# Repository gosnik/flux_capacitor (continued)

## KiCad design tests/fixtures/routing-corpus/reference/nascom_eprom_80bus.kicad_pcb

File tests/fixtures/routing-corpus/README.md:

# Real-board routing corpus

This directory replaces Flux's generated 4--20 component routing boards with a deliberately small
progression derived from the open-source
[KiCadRoutingTools stress corpus](https://github.com/drandyhaas/KiCadRoutingTools/tree/main/tests/stress)
and its [real-board routing discussion](https://github.com/drandyhaas/KiCadRoutingTools/discussions/117).

The important policy is monotonic progressive activation. A qualified tier always remains in the
routine run, and permanently unlocks the next tier as the single capability probe. Higher
levels remain available for focused inspection, but are not silently added to every build merely
because their files exist.

| Level | Board | Upstream stress set | Current gate | Purpose |
| ---: | --- | --- | --- | --- |
| 0 | `pt2399_delay` | set13 | mandatory, passing | Requalified under original project rules; 50 connections, zero errors/opens; straight tracks |
| 1 | `bm_svf` | set15 | unlocked | Always-run analog module probe; 78 seeded connections with residual overflow |
| 2 | `ft2232h_jtag` | set5 | locked | 117 connections; compact 64-pin USB/JTAG fanout |
| 3 | `gb_nintendo_power` | set24 | locked | 148 connections; 80-pad IC and parallel memory buses |
| 4 | `nascom_eprom_80bus` | set23 | locked | 415 connections; repeated DIP sockets and card-edge bus |

`manifest.json` is authoritative for source repository, exact commit, original path, license,
source hash, prepared-board hash, routed-reference hash, project hash, inventory, and current gate.
The board beside each project is the stripped routing input. `reference/` contains the normalized
human-routed board so later quality grading can compare against ground truth rather than assuming
zero source DRC findings. Full upstream license texts are under `licenses/`.

The 2026-09-06 rule-context audit found that the final DRC candidate lacked its
sibling project and was checked under KiCad defaults. The unchanged Tier-0 copper
has 199 track-width and 9 drill-spacing errors under the original project, with
zero opens. The manifest keeps Tier 0's mandatory `qualified` gate so the corrected
test fails visibly; it has not been downgraded to hide the regression. Tier 0 must
be genuinely recovered before promoting Tier 1. See
`reports/diagnoses/2026-09-06-tier0-project-rule-context.json` at the repository root.

Tier 0 was genuinely restored on 2026-09-07 after source-rule import, source-hole
preservation, committed-context retries and run-aligned PH corner seeds. The
curved-mode corpus invocation at that point passed: 82 tracks, 152 arcs, four vias, zero
unfinished bends and clean original-project KiCad DRC. An unspecified CLI pitch
is raised to the shared validator's source-rule floor; explicit values remain
validated. See `reports/benchmark_history/2026-09-07-default-rule-pitch.json`.
Tier 1 remains the frontier; its latest 600-second diagnostic probe timed out in
regional repair, and its 78 selected paths are not legal final copper.

## Preparation

The inputs were prepared from pinned upstream revisions with KiCadRoutingTools commit
`661c88b3c3b0ebc9ade65eab63d30b1cde217fb4`, using `tests/stress/prep_set2.py` and pcbnew 9.0.8.
The only compatibility adjustment supplied a null error-handler argument to the KiCad 9
`GetBoardPolygonOutlines` overload. Preparation normalized the source, removed tracks, vias and
copper zones, retained rule areas, rebuilt Edge.Cuts, removed non-routing graphics, and preserved
the sibling project settings. This is recorded in the manifest rather than treated as upstream
source identity.

## Running the progression

The ordinary test runs every qualified tier plus the first unlocked tier:

```sh
ctest --test-dir build/dev -R flux_cli_routing_corpus_unlocked --output-on-failure
```

Inspect progressively larger capability levels without routing every board:

```sh
python3 tests/python/verify_routing_corpus.py \
  --flux-cli build/dev/flux-cli \
  --corpus tests/fixtures/routing-corpus \
  --level 2
```

`--level all` verifies provenance and strict import for the whole curated set. Locked tiers are not
routed unless they become unlocked. A qualified board must keep completing; the unlocked board
always receives a bounded routing attempt. If that attempt satisfies its qualification target, the
harness fails with an explicit promotion request: change it from `unlocked` to `qualified` and
change the next locked tier to `unlocked` in the same revision. This makes unlocking permanent
without allowing a test process to mutate policy. The source and reference files are hashed before
and after every run.

Every tier now requires `detailed_complete`; a zero-overflow global plan alone cannot trigger
promotion. `detailed_complete` is the final-copper qualification. Such a tier must produce an
exported KiCad
board with zero structural errors, open connections, and represented copper violations. Only after
those exact gates and an error-level external KiCad DRC pass does the harness render one
2400-pixel PNG per enabled copper layer (with `Edge.Cuts` as context) under the configured artifact
directory. Incomplete previews are never labelled or rendered as final copper. CTest writes these review artifacts below
`build/release/tests/routing-corpus-artifacts/`.

Final DRC now requires a byte-identical project and any custom-rule sidecar under
the candidate's basename. Their hashes are recorded in `kicad-drc.context.json`.
They are also published beside accepted copper. Rejected copper and its rule
context are retained under `analysis/kicad-drc-rejected`, not as final output.

Every tier run records diagnostic telemetry and writes bounded, non-authoritative analysis PNGs
under `artifacts/tier-<level>-<board>/analysis`. The images are emitted for successful,
incomplete, and timed-out routing attempts. `--failed-route-png-dir` remains available only to
override that analysis root, for example:

```sh
python3 tests/python/verify_routing_corpus.py \
  --flux-cli build/dev/flux-cli \
  --corpus tests/fixtures/routing-corpus \
  --board bm_svf \
  --failed-route-png-dir build/failed-route-previews \
  --failed-route-png-mode both \
  --max-failed-route-png-results 8
```

The harness ranks completed regional candidates by topology
and mutual-clearance failures, and writes layer copper, whole provisional-board, full-context
quintic PH Bezier controls, and automatically cropped control close-ups. A JSON manifest records the candidate/window identity and explicitly marks
the output as diagnostic rather than accepted copper. `copper` and `spline` modes may be selected
individually. Rendering also runs after a board timeout, using every complete telemetry event that
was flushed before cancellation.

Useful KiCadRoutingTools ideas retained in Flux's harness are immutable pinned sources, paired
human references, manifest provenance, bounded per-board execution, deterministic replay inputs,
and progressive corpus qualification. Their large queue/agent orchestration is intentionally not
copied into the routine test path.

The current default is straight-section routing. Tier 0 has been rechecked repeatedly:
243 horizontal/vertical/45-degree tracks, zero arcs, five vias, all 50 connections and clean
original-project KiCad DRC. The runner independently audits exported segment angles. The arc-count and rounded-bend requirements are retained in `curved_expected`
and selected by `./run_tiers.sh --track-geometry curved`. Fabrication, connectivity and
external DRC requirements are identical in both modes. Tier 1 remains unqualified.
See `reports/benchmark_history/2026-09-07-tier-resolution/summary.json` for the current
experiments and `reports/benchmark_history/2026-09-07-straight-routing-summary.json` for
the earlier straight-mode baseline and rejected controls.

## Adopted alternative boards

A separately staged [alternative Tier 2–4 corpus](alternatives/README.md) contains
FT2232H JTAG/UART, Nintendo Power cartridge and Nascom EPROM inputs with clean
strict-import and stripped-board DRC checks. Selection evidence and reference
caveats are documented there. These boards now replace the source-blocked levels 2–4 in the active manifest;
all remain locked and unqualified. The former Zigbee, CH32V003 and USB-GPIB
inputs remain in `compatibility/manifest.json` as source-compatibility regressions.
The existing Tier-0 and Tier-1 entries are byte-for-byte equivalent JSON objects.
New boards carry their KRT preparation revision per entry; initial provenance
above continues to describe levels 0–1 and the compatibility corpus.

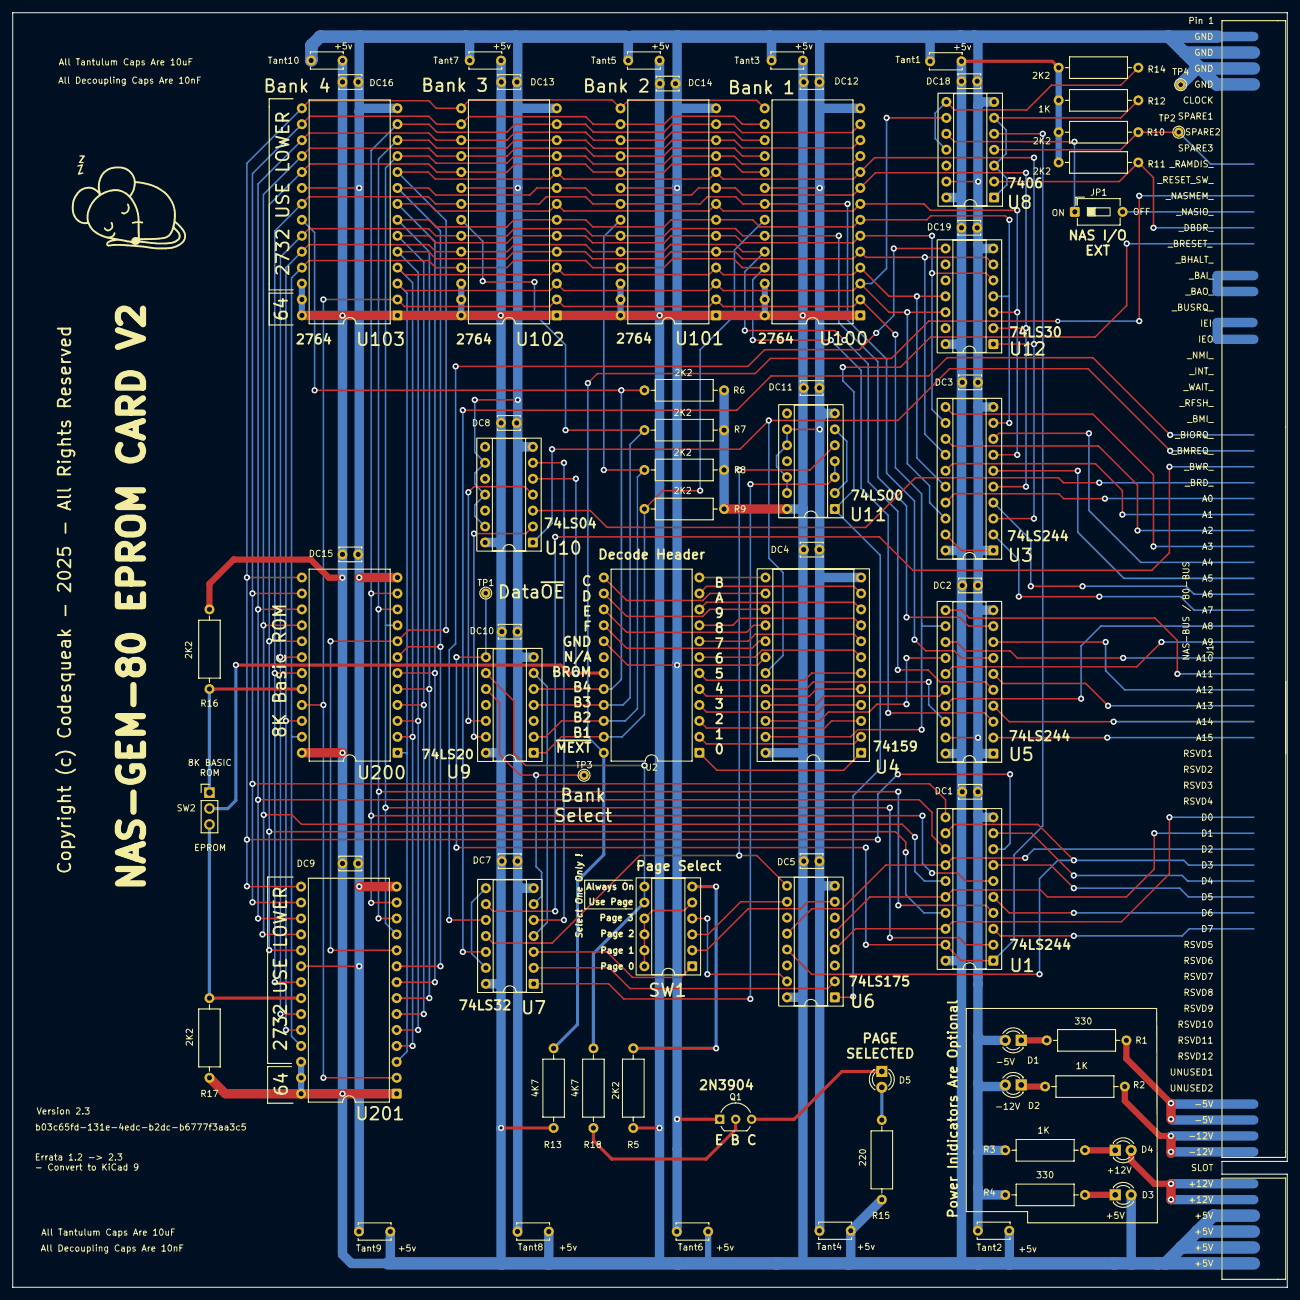
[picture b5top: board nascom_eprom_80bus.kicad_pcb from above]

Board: 2 copper layers, 203.2 x 203.2 mm, 79 parts (1 on the bottom side), 116 nets.

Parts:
D1, D2, D3, D4, D5: LED; LED_D3.0mm
DC1, DC2, DC3, DC4, DC5, DC7, DC8, DC9, DC10, DC11, DC12, DC13, DC14, DC15, DC16, DC18, DC19: 10nF; C_Disc_D3.4mm_W2.1mm_P2.50mm
G1: LOGO; sleepymouse_small
G001: LOGO; qr-code
J1: Conn_01x80NasBus; 80BusEdgeConnector
JP1: Link 1; SW_DIP_SPSTx01_Slide_6.7x4.1mm_W7.62mm_P2.54mm_LowProfile
Q1: 2N3904; TO-92_Inline_Wide
R1, R4, R15: 330; R_Axial_DIN0309_L9.0mm_D3.2mm_P12.70mm_Horizontal
R2, R3: 1k; R_Axial_DIN0309_L9.0mm_D3.2mm_P12.70mm_Horizontal
R5, R6, R7, R8, R9, R10, R11, R14, R16, R17: 2K2; R_Axial_DIN0309_L9.0mm_D3.2mm_P12.70mm_Horizontal
R12: 1K; R_Axial_DIN0309_L9.0mm_D3.2mm_P12.70mm_Horizontal
R13, R18: 4K7; R_Axial_DIN0309_L9.0mm_D3.2mm_P12.70mm_Horizontal
SW1: SW_DIP_x06; DIP-12_W7.62mm_Socket
SW2: SW_SPDT; PinHeader_1x03_P2.54mm_Vertical
TP1: Data ~OE~; TestPoint_THTPad_D1.5mm_Drill0.7mm
TP2: ~RAMDIS~; TestPoint_THTPad_D1.5mm_Drill0.7mm
TP3: Bank Select; TestPoint_THTPad_D1.5mm_Drill0.7mm
TP4: 0V / Ground; TestPoint_THTPad_D1.5mm_Drill0.7mm
Tant1, Tant2, Tant3, Tant4, Tant5, Tant6, Tant7, Tant8, Tant9, Tant10: 10uF; C_Disc_D5.0mm_W2.5mm_P5.00mm
U1, U3, U5: 74LS244; DIP-20_W7.62mm_Socket
U2: DecodeHeader; DIP-24_W15.24mm
U4: 74159; DIP-24_W15.24mm_Socket
U6: 74LS175; DIP-16_W7.62mm_Socket
U7: 74LS32; DIP-14_W7.62mm_Socket
U8: 7406; DIP-14_W7.62mm_Socket
U9: 74LS20; DIP-14_W7.62mm_Socket
U10: 74LS04; DIP-14_W7.62mm_Socket
U11: 74LS00; DIP-14_W7.62mm_Socket
U12: 74LS30; DIP-14_W7.62mm_Socket
U100, U101, U102, U103, U201: 2764; DIP-28_W15.24mm
U200: MK36000_8K_ROM; DIP-24_W15.24mm

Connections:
8K_ROM: SW2.2 (B), U2.19 (~8KROM), U10.5
+12V: D4.2 (A), J1.73 (Pin_73_+12v), J1.74 (Pin_74_+12v)
-5V: J1.68 (Pin_68_-5v), J1.69 (Pin_69_-5v), R1.2
-12V: J1.70 (Pin_70_-12v), J1.71 (Pin_71_-12v), R2.2
/BA0: U3.3 (O3b), U12.1, U100.10 (A0), U101.10 (A0), U102.10 (A0), U103.10 (A0), U200.8 (A0), U201.10 (A0)
/BA1: U3.5 (O2b), U12.2, U100.9 (A1), U101.9 (A1), U102.9 (A1), U103.9 (A1), U200.7 (A1), U201.9 (A1)
/BA2: U3.7 (O1b), U12.3, U100.8 (A2), U101.8 (A2), U102.8 (A2), U103.8 (A2), U200.6 (A2), U201.8 (A2)
/BA3: U3.9 (O0b), U12.4, U100.7 (A3), U101.7 (A3), U102.7 (A3), U103.7 (A3), U200.5 (A3), U201.7 (A3)
/BA4: U3.12 (O3a), U12.5, U100.6 (A4), U101.6 (A4), U102.6 (A4), U103.6 (A4), U200.4 (A4), U201.6 (A4)
/BA5: U3.14 (O2a), U12.6, U100.5 (A5), U101.5 (A5), U102.5 (A5), U103.5 (A5), U200.3 (A5), U201.5 (A5)
/BA6: U3.16 (O1a), U12.11, U100.4 (A6), U101.4 (A6), U102.4 (A6), U103.4 (A6), U200.2 (A6), U201.4 (A6)
/BA7: U3.18 (O0a), U8.9, U12.12, U100.3 (A7), U101.3 (A7), U102.3 (A7), U103.3 (A7), U200.1 (A7), U201.3 (A7)
/BA8: U5.3 (O3b), U100.25 (A8), U101.25 (A8), U102.25 (A8), U103.25 (A8), U200.23 (A8), U201.25 (A8)
/BA9: U5.5 (O2b), U100.24 (A9), U101.24 (A9), U102.24 (A9), U103.24 (A9), U200.22 (A9), U201.24 (A9)
/BA10: U5.7 (O1b), U100.21 (A10), U101.21 (A10), U102.21 (A10), U103.21 (A10), U200.19 (A10), U201.21 (A10)
/BA11: U5.9 (O0b), U100.23 (A11), U101.23 (A11), U102.23 (A11), U103.23 (A11), U200.18 (A11), U201.23 (A11)
/BA12: U4.23 (A0), U5.12 (O3a), U100.2 (A12), U101.2 (A12), U102.2 (A12), U103.2 (A12), U200.21 (A12), U201.2 (A12)
/BD0: U1.2 (I0a), U100.11 (D0), U101.11 (D0), U102.11 (D0), U103.11 (D0), U200.9 (DQ0), U201.11 (D0)
/BD1: U1.4 (I1a), U100.12 (D1), U101.12 (D1), U102.12 (D1), U103.12 (D1), U200.10 (DQ1), U201.12 (D1)
/BD2: U1.6 (I2a), U100.13 (D2), U101.13 (D2), U102.13 (D2), U103.13 (D2), U200.11 (DQ2), U201.13 (D2)
/BD3: U1.8 (I3a), U100.15 (D3), U101.15 (D3), U102.15 (D3), U103.15 (D3), U200.13 (DQ3), U201.15 (D3)
/BD4: U1.11 (I0b), U100.16 (D4), U101.16 (D4), U102.16 (D4), U103.16 (D4), U200.14 (DQ4), U201.16 (D4)
/BD5: U1.13 (I1b), U100.17 (D5), U101.17 (D5), U102.17 (D5), U103.17 (D5), U200.15 (DQ5), U201.17 (D5)
/BD6: U1.15 (I2b), U100.18 (D6), U101.18 (D6), U102.18 (D6), U103.18 (D6), U200.16 (DQ6), U201.18 (D6)
/BD7: U1.17 (I3b), U100.19 (D7), U101.19 (D7), U102.19 (D7), U103.19 (D7), U200.17 (DQ7), U201.19 (D7)
A0: J1.30, U3.17 (I3b)
A1: J1.31, U3.15 (I2b)
A2: J1.32, U3.13 (I1b)
A3: J1.33, U3.11 (I0b)
A4: J1.34, U3.8 (I3a)
A5: J1.35, U3.6 (I2a)
A6: J1.36, U3.4 (I1a)
A7: J1.37, U3.2 (I0a)
A8: J1.38, U5.17 (I3b)
A9: J1.39, U5.15 (I2b)
A10: J1.40, U5.13 (I1b)
A11: J1.41, U5.11 (I0b)
A12: J1.42, U5.8 (I3a)
A13: J1.43, U5.6 (I2a)
A14: J1.44, U5.4 (I1a)
A15: J1.45, U5.2 (I0a)
Bank1: R9.1, U2.23 (~Bank1), U9.1, U100.22 (~OE)
Bank2: R8.1, U2.22 (~Bank2), U9.2, U101.22 (~OE)
Bank3: R7.1, U2.21 (~Bank3), U9.4, U102.22 (~OE)
Bank4: R6.1, U2.20 (~Bank4), U9.5, U103.22 (~OE)
D0: J1.50, U1.18 (O0a), U6.4 (D0)
D1: J1.51, U1.16 (O1a), U6.5 (D1)
D2: J1.52, U1.14 (O2a), U6.12 (D2)
D3: J1.53, U1.12 (O3a), U6.13 (D3)
D4: J1.54, U1.9 (O0b)
D5: J1.55, U1.7 (O1b)
D6: J1.56, U1.5 (O2b)
D7: J1.57, U1.3 (O3b)
GND: D1.2 (A), D2.2 (A), DC1.2, DC2.2, DC3.2, DC4.2, DC5.2, DC7.2, DC8.2, DC9.2, DC10.2, DC11.2, DC12.2, DC13.2, DC14.2, DC15.2, DC16.2, DC18.2, DC19.2, J1.1 (Pin_1_0v), J1.2 (Pin_2_0v), J1.3 (Pin_3_0v), J1.4 (Pin_4_0v), Q1.1 (E), R3.2, R4.2, TP4.1, Tant1.2, Tant2.2, Tant3.2, Tant4.2, Tant5.2, Tant6.2, Tant7.2, Tant8.2, Tant9.2, Tant10.2, U1.10 (GND), U2.17 (GND), U3.1 (OEa), U3.10 (GND), U3.19 (OEb), U4.12 (GND), U4.18 (~E0), U5.1 (OEa), U5.10 (GND), U5.19 (OEb), U6.8 (GND), U7.7 (GND), U8.7 (GND), U8.13, U9.7 (GND), U10.7 (GND), U10.9, U10.11, U10.13, U11.7 (GND), U11.9, U11.10, U11.12, U11.13, U12.7 (GND), U100.14 (GND), U100.20 (~CE), U101.14 (GND), U101.20 (~CE), U102.14 (GND), U102.20 (~CE), U103.14 (GND), U103.20 (~CE), U200.12 (VSS), U201.14 (GND), U201.20 (~CE)
unnamed: D1.1 (K), R1.1
unnamed: D2.1 (K), R2.1
unnamed: D3.1 (K), R4.1
unnamed: D4.1 (K), R3.1
unnamed: D5.2 (A), R15.2
unnamed: D5.1 (K), Q1.3 (C)
unnamed: J1.16, J1.17
unnamed: J1.19, J1.20
unnamed: JP1.1 (A), U8.10
unnamed: Q1.2 (B), R18.1
unnamed: R5.2, SW1.6
unnamed: R12.2, U8.1, U8.3, U8.6
unnamed: R14.1, U8.8, U8.11
unnamed: R18.2, SW1.7, SW1.8, U9.9
unnamed: SW1.1, U7.3
unnamed: SW1.5, SW1.9, SW1.10, SW1.11, SW1.12
unnamed: R16.2, SW2.1 (A), U200.20 (~OE)
unnamed: R17.2, SW2.3 (C), U201.22 (~OE)
unnamed: TP3.1, U7.6, U9.10
unnamed: TP1.1, U1.1 (OEa), U1.19 (OEb), U8.5, U9.8
unnamed: U2.1 (Block0), U4.1 (~S0)
unnamed: U2.2 (Block1), U4.2 (~S1)
unnamed: U2.3 (Block2), U4.3 (~S2)
unnamed: U2.4 (Block3), U4.4 (~S3)
unnamed: U2.5 (Block4), U4.5 (~S4)
unnamed: U2.6 (Block5), U4.6 (~S5)
unnamed: U2.7 (Block6), U4.7 (~S6)
unnamed: U2.8 (Block7), U4.8 (~S7)
unnamed: U2.9 (Block8), U4.9 (~S8)
unnamed: U2.10 (Block9), U4.10 (~S9)
unnamed: U2.11 (BlockA), U4.11 (~S10)
unnamed: U2.12 (BlockB), U4.13 (~S11)
unnamed: U2.13 (BlockC), U4.14 (~S12)
unnamed: U2.14 (BlockD), U4.15 (~S13)
unnamed: U2.15 (BlockE), U4.16 (~S14)
unnamed: U2.16 (BlockF), U4.17 (~S15)
unnamed: U4.22 (A1), U5.14 (O2a)
unnamed: U4.21 (A2), U5.16 (O1a)
unnamed: U4.20 (A3), U5.18 (O0a)
unnamed: U6.9 (Cp), U7.11, U11.5
unnamed: U6.2 (Q0), U7.2
unnamed: SW1.2, U6.7 (Q1)
unnamed: SW1.3, U6.10 (Q2)
unnamed: SW1.4, U6.15 (Q3)
unnamed: U7.4, U9.6
unnamed: U7.8, U7.13
unnamed: U9.13, U10.2
unnamed: U9.12, U10.4
unnamed: U7.5, U10.6
unnamed: U11.2, U11.6
unnamed: U7.10, U12.8
PAGE_0: U7.1, U11.3, U11.4
VCC: D3.2 (A), DC1.1, DC2.1, DC3.1, DC4.1, DC5.1, DC7.1, DC8.1, DC9.1, DC10.1, DC11.1, DC12.1, DC13.1, DC14.1, DC15.1, DC16.1, DC18.1, DC19.1, J1.75 (Pin_75_+5v), J1.76 (Pin_76_+5v), J1.77 (Pin_77__+5v), J1.78 (Pin_78__+5v), R5.1, R6.2, R7.2, R8.2, R9.2, R10.1, R11.1, R12.1, R13.1, R14.2, R15.1, R16.1, R17.1, Tant1.1, Tant2.1, Tant3.1, Tant4.1, Tant5.1, Tant6.1, Tant7.1, Tant8.1, Tant9.1, Tant10.1, U1.20 (VCC), U3.20 (VCC), U4.24 (VCC), U5.20 (VCC), U6.16 (VCC), U7.14 (VCC), U8.14 (VCC), U9.14 (VCC), U10.14 (VCC), U11.14 (VCC), U12.14 (VCC), U100.1 (VPP), U100.26 (NC), U100.27 (~PGM), U100.28 (VCC), U101.1 (VPP), U101.26 (NC), U101.27 (~PGM), U101.28 (VCC), U102.1 (VPP), U102.26 (NC), U102.27 (~PGM), U102.28 (VCC), U103.1 (VPP), U103.26 (NC), U103.27 (~PGM), U103.28 (VCC), U200.24 (VCC), U201.1 (VPP), U201.26 (NC), U201.27 (~PGM), U201.28 (VCC)
~BIORQ: J1.26, U7.12
~BMREQ: J1.27, U4.19 (~E1), U10.1
~BRD: J1.29, U10.3
~BRESET: J1.14, U6.1 (~Mr), U11.1
~BWR: J1.28, U7.9
~DBDR: J1.13, R11.2, U8.2
~NASIO: J1.12, JP1.2 (B)
~NASMEM: J1.11, R13.2, U2.24 (~MEXT)
~RAMDIS: J1.9, R10.2, TP2.1, U8.4

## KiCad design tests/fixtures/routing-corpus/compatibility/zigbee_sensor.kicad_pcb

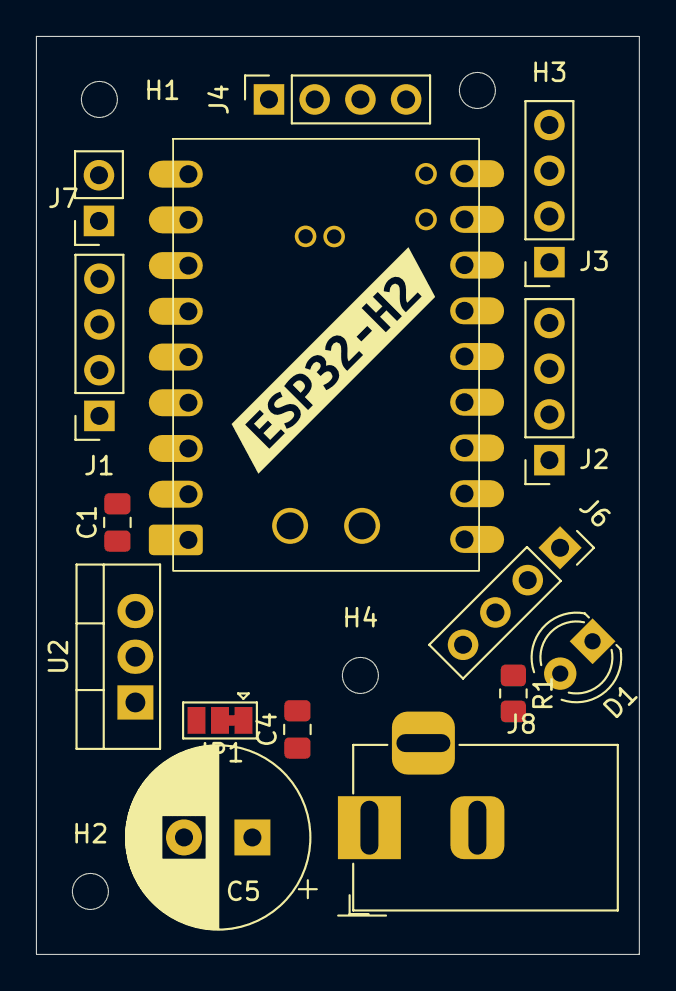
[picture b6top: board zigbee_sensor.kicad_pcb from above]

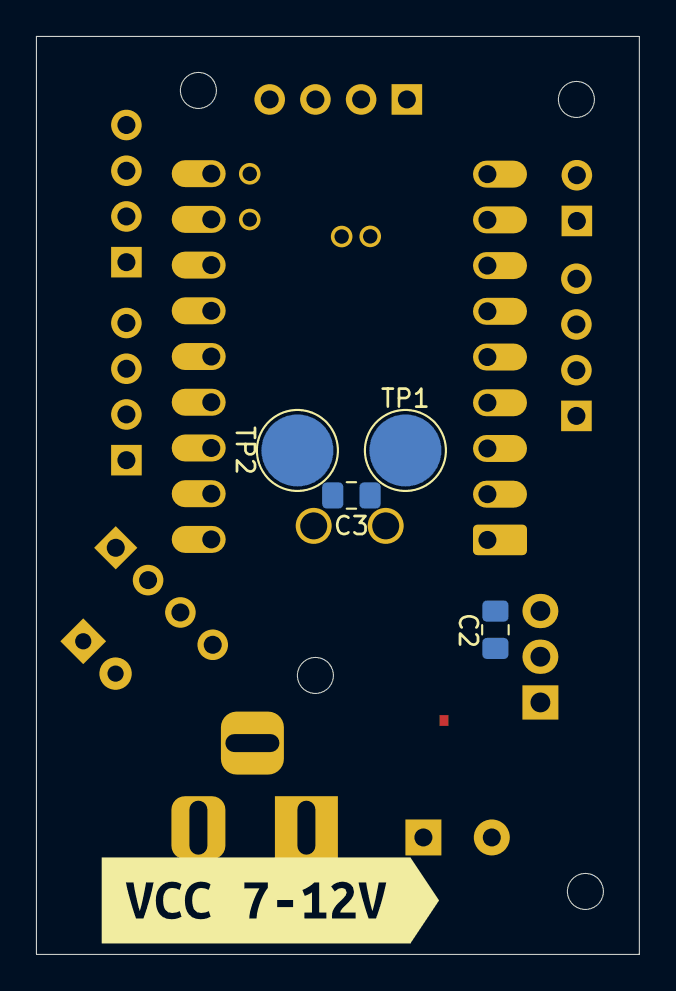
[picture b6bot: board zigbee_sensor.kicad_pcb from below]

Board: 2 copper layers, 33.5 x 51.0 mm, 25 parts (5 on the bottom side), 26 nets, no tracks yet.

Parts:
C1, C2, C3, C4: C; C_0805_2012Metric_Pad1.18x1.45mm_HandSolder
C5: C_Polarized; CP_Radial_D10.0mm_P3.80mm
D1: LED; LED_D4.0mm
H1, H2, H3, H4: MountingHole; MountingHole_2mm
J1, J2, J3, J4, J6: Conn_01x04_Socket; PinSocket_1x04_P2.54mm_Vertical
J7: Conn_01x02_Socket; PinSocket_1x02_P2.54mm_Vertical
J8: Barrel_Jack_Switch; BarrelJack_Horizontal
JP1: SolderJumper_3_Bridged12; SolderJumper-3_P1.3mm_Bridged12_Pad1.0x1.5mm
R1: R; R_0805_2012Metric_Pad1.20x1.40mm_HandSolder
TP1, TP2: TestPoint; TestPoint_Pad_D4.0mm
U1: ESP32-H2-SUPERMINI; ESP32H2-Supermini
U2: LM7805_TO220; TO-220-3_Vertical
kibuzzard-67CC80C3: G***; kibuzzard-67CC80C3
kibuzzard-67CC814E: G***; kibuzzard-67CC814E

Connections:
+5V: C1.1, C2.1, J6.4, JP1.1 (A), R1.2, U1.9 (5V), U2.3 (VO)
+12V: JP1.3 (B), U2.1 (VI)
B+: C3.1, TP1.1, U1.23 (B+)
B-: C3.2, TP2.1, U1.24 (B-)
GND: C1.2, C2.2, C4.2, C5.2, D1.1 (K), J6.1, J8.2, J8.3, U1.8 (GND), U2.2 (GND)
GPIO0: J2.1, U1.17 (IO0)
GPIO1: J2.2, U1.16 (IO1)
GPIO2: J2.3, U1.15 (IO2)
GPIO3: J2.4, U1.14 (IO3)
GPIO4: J3.1, U1.13 (IO4)
GPIO5: J3.2, U1.12 (IO5)
GPIO8: J3.3, U1.11 (IO8)
GPIO9: J7.2, U1.1 (IO9)
GPIO10: J7.1, U1.2 (IO10)
GPIO11: J1.4, U1.3 (IO11)
GPIO12: J1.3, U1.4 (IO12)
GPIO13: J1.2, U1.5 (IO13)
GPIO14: J1.1, U1.6 (IO14)
GPIO22: J4.1, U1.10 (IO22)
GPIO23: J6.2, U1.18 (IO23)
GPIO24: J6.3, U1.19 (IO24)
GPIO25: J4.2, U1.20 (IO25)
GPIO26: J4.3, U1.22 (IO26)
GPIO27: J3.4, U1.21 (IO27)
unnamed: D1.2 (A), R1.1
VCC: C4.1, C5.1, J8.1, JP1.2 (C)
